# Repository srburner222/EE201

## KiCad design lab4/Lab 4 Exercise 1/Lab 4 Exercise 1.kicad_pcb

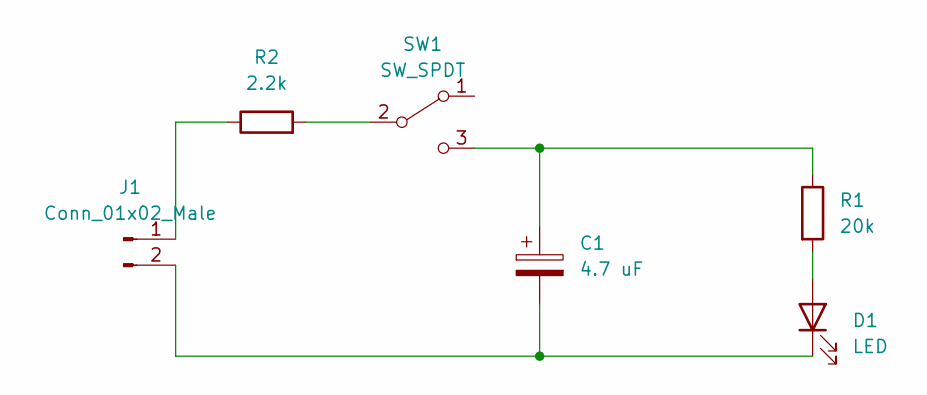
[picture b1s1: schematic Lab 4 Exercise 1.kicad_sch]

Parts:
C1: 4.7 uF; C_Radial_D5.0mm_H5.0mm_P2.00mm
D1: LED; LED_D5.0mm
J1: Conn_01x02_Male; JST_PH_B2B-PH-K_1x02_P2.00mm_Vertical
R1: 20k; R_Axial_DIN0516_L15.5mm_D5.0mm_P20.32mm_Horizontal
R2: 2.2k; R_Axial_DIN0516_L15.5mm_D5.0mm_P20.32mm_Horizontal
SW1: SW_SPDT; SW_E-Switch_EG1224_SPDT_Angled

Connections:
unnamed: C1.1, R1.1, SW1.3 (C)
unnamed: C1.2, D1.1 (K), J1.2
unnamed: D1.2 (A), R1.2
unnamed: J1.1, R2.1
unnamed: R2.2, SW1.2 (B)

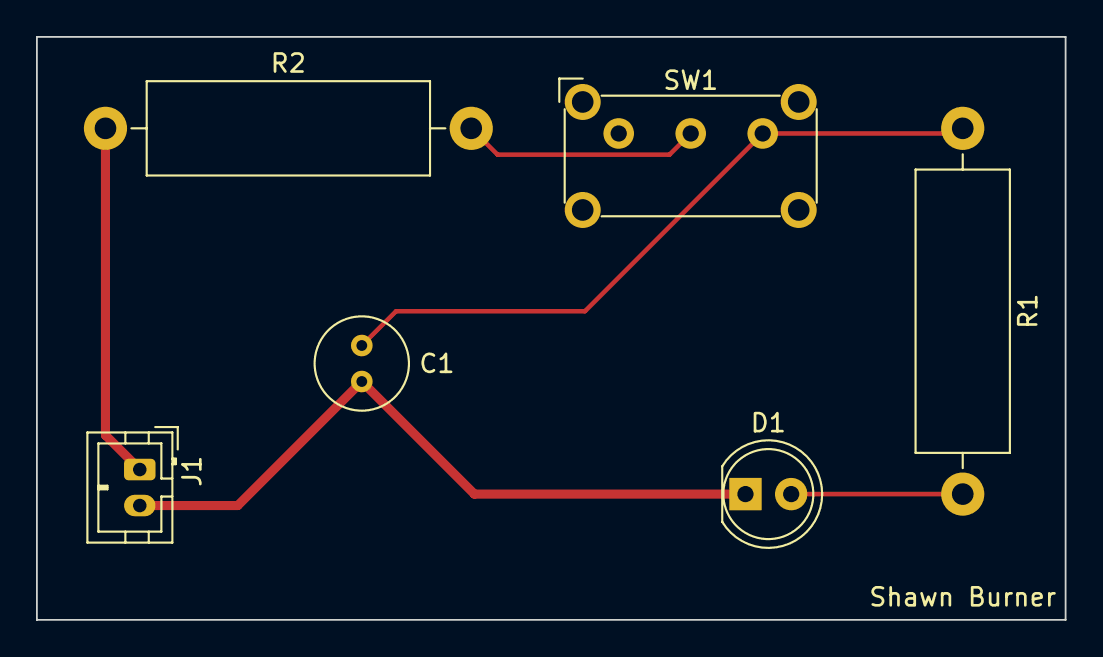
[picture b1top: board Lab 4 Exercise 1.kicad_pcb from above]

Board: 2 copper layers, 57.2 x 32.4 mm, 6 parts (0 on the bottom side), 5 nets.

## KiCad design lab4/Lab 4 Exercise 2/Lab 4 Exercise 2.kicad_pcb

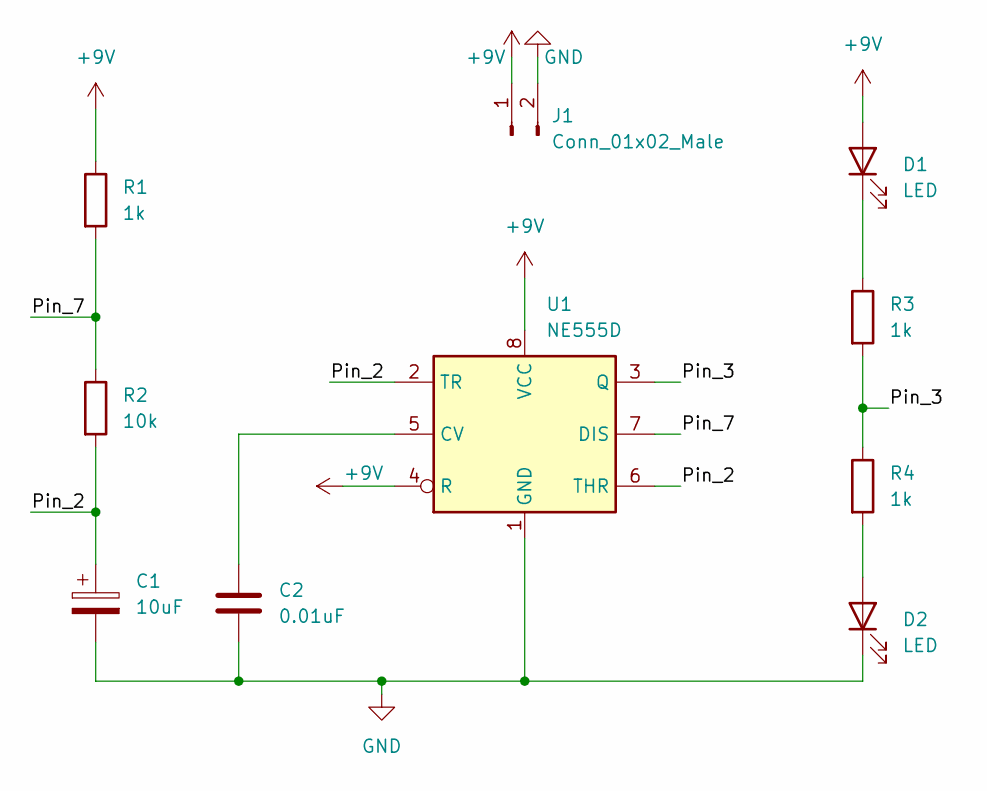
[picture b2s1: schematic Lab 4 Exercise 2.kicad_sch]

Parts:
C1: 10uF; CP_EIA-3216-18_Kemet-A_Pad1.58x1.35mm_HandSolder
C2: 0.01uF; C_0805_2012Metric_Pad1.18x1.45mm_HandSolder
D1, D2: LED; LED_1206_3216Metric_Pad1.42x1.75mm_HandSolder
J1: Conn_01x02_Male; TerminalBlock_bornier-2_P5.08mm
R1, R3, R4: 1k; R_0805_2012Metric_Pad1.20x1.40mm_HandSolder
R2: 10k; R_0805_2012Metric_Pad1.20x1.40mm_HandSolder
U1: NE555D; SOIC-8-1EP_3.9x4.9mm_P1.27mm_EP2.29x3mm

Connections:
+9V: D1.2 (A), J1.1, R1.1, U1.4 (R), U1.8 (VCC)
/Pin_2: C1.1, R2.2, U1.2 (TR), U1.6 (THR)
/Pin_3: R3.2, R4.1, U1.3 (Q)
/Pin_7: R1.2, R2.1, U1.7 (DIS)
GND: C1.2, C2.2, D2.1 (K), J1.2, U1.1 (GND)
unnamed: C2.1, U1.5 (CV)
unnamed: D1.1 (K), R3.1
unnamed: D2.2 (A), R4.2

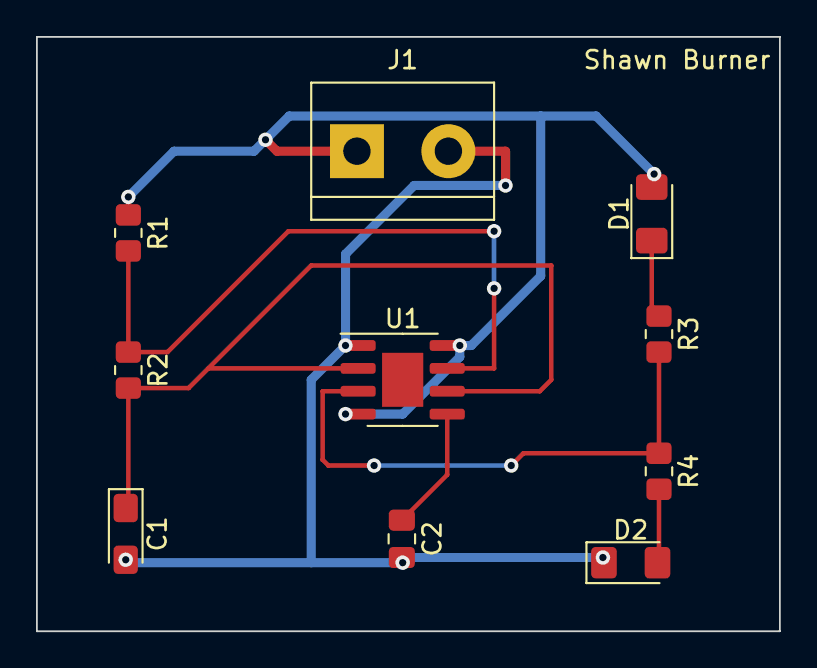
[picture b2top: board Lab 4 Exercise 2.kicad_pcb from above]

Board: 2 copper layers, 41.3 x 33.0 mm, 10 parts (0 on the bottom side), 8 nets.

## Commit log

2023-01-13 Inital commit
2023-01-13 inital readme commit
2023-01-13 added content
2023-01-13 formatting
2023-01-20 arduino setup
2023-01-22 arduino code
2023-02-01 schematics
2023-02-08 soldering images
2023-02-14 final schematics and pcbs
2023-02-17 gerber files
2023-03-11 added PCB files
2023-03-11 arduometer working
